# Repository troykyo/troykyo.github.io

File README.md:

This is a little site about Troy Nachtigall

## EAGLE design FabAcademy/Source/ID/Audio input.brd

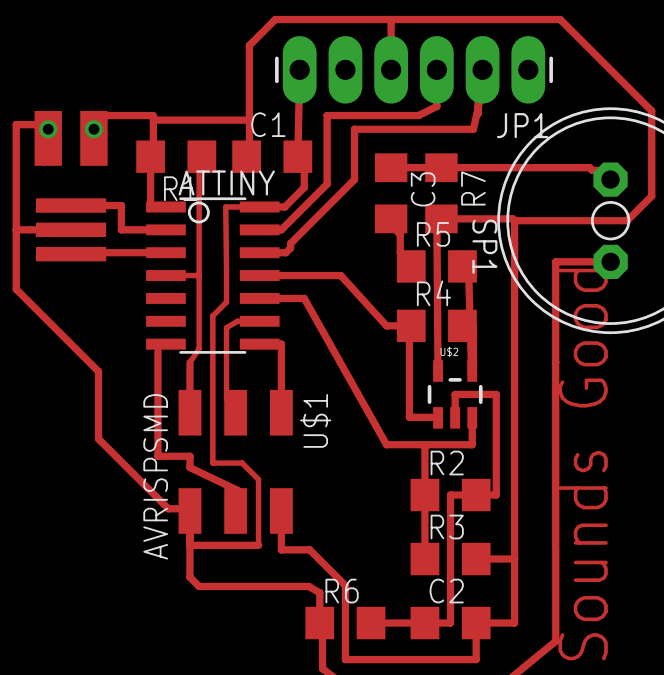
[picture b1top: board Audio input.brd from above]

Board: 2 copper layers, 16 parts (0 on the bottom side), 15 nets.

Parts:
ATTINY: ATTINY44-SSU; SOIC14
C1, C2, C3: 1206
JP1: 1X06_LONGPADS
QUARTZ: RESONATOR; EFOBM
R1, R2, R3, R4, R5, R6, R7: 1206
SP1: AL11P
U$1: AVRISPSMD; 2X03SMD
U$2: OPA344; SOT23-5

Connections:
GND: ATTINY.14, C1.2, C2.1, JP1.6, QUARTZ.2, R2.2, R6.1, R6.2, SP1.-, U$1.6, U$2.2
MIC+: C3.1, R7.1, SP1.+
MICCAP: C3.2, R5.1
MISO: ATTINY.8, U$1.1
MOSI: ATTINY.7, U$1.4
OPAI+: ATTINY.10, R2.1, R3.1, U$2.3
OPAI-: R4.2, R5.2, U$2.4
OPAOV: ATTINY.11, R4.1, U$2.1
RST: ATTINY.4, R1.1, U$1.5
RX: ATTINY.12, JP1.2
SCK: ATTINY.9, U$1.3
TX: ATTINY.13, JP1.3
VCC: ATTINY.1, C1.1, C2.2, JP1.4, R1.2, R3.2, R7.2, U$1.2, U$2.5
XTAL1: ATTINY.2, QUARTZ.3
XTAL2: ATTINY.3, QUARTZ.1

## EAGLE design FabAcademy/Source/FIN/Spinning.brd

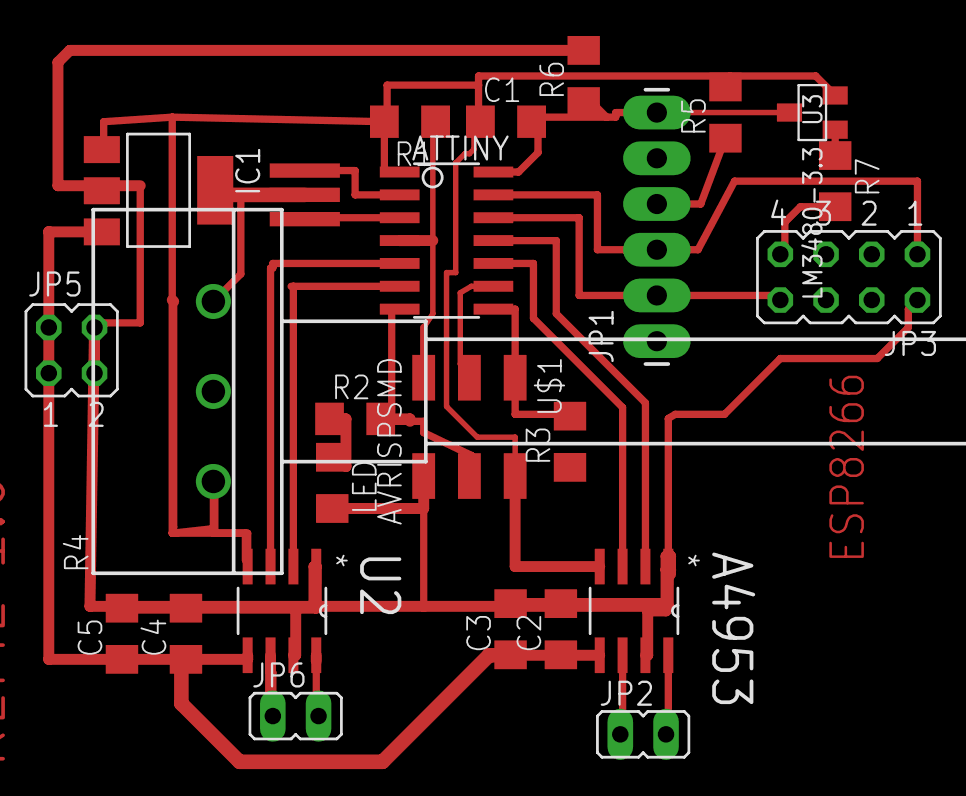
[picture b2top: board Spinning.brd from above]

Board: 2 copper layers, 25 parts (0 on the bottom side), 22 nets.

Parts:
A4953: ACS712ELCTR-05B-T; SOIC127P600X175-8N
ATTINY: ATTINY44-SSU; SOIC14
C1: 1uF; 1206
C2, C4: .1uF; 1206
C3, C5: 10uF; 1206
IC1: REG1118; SOT223
JP1: 1X06_LONGPADS
JP2, JP6: JP1
JP3: JP4Q
JP5: JP2Q
LED: 1206
QUARTZ: RESONATOR; EFOBM
R1: 10k; 1206
R2: 1K; 1206
R3: 1k; 1206
R4: CIP20C-6MM
R5, R6, R7: 0; 1206
U2: ACS712ELCTR-05B-T; SOIC127P600X175-8N
U3: LM3480-3.3; SOT-23-3
U$1: AVRISPSMD; 2X03SMD

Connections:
GND: A4953.1, A4953.7, ATTINY.14, C1.2, C2.2, C3.2, C4.2, C5.2, IC1.2, JP1.6, JP3.2, JP5.3, JP5.4, LED.2, QUARTZ.2, R4.E, R6.1, R6.2, U2.1, U2.7, U3.3, U$1.6
IN1A: A4953.3, ATTINY.10
IN1B: ATTINY.5, U2.3
IN2A: A4953.2, ATTINY.11
IN2B: ATTINY.6, U2.2
LEDRES: LED.1, R2.1
LEDRES1: R3.1, R4.S
MISO: ATTINY.8, R3.2, U$1.1
MOSI: ATTINY.7, R2.2, U$1.4
OUT1A: A4953.6, JP2.1
OUT1B: JP6.1, U2.6
OUT2A: A4953.8, JP2.2
OUT2B: JP6.2, U2.8
RST: ATTINY.4, R1.1, U$1.5
RX: ATTINY.12, JP1.2, JP3.8
SCK: ATTINY.9, U$1.3
TX: ATTINY.13, JP1.3, JP3.1
VBB: A4953.5, C2.1, C3.1, C4.1, C5.1, IC1.3, JP5.1, JP5.2, U2.5
VCC: A4953.4, ATTINY.1, C1.1, IC1.1, JP1.4, R1.2, R4.A, R5.1, R5.2, U2.4, U3.2, U$1.2
VCCESP: JP3.7, R7.1, R7.2, U3.1
XTAL1: ATTINY.2, QUARTZ.3
XTAL2: ATTINY.3, QUARTZ.1

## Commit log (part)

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2015-01-20 Initialization
2015-01-20 First Content
2015-01-20 First Post
2015-01-22 now with bootstrap
2015-01-22 Tom Theme Change
2015-01-22 Changed to Twitter theme.
2015-01-22 Name fix
2015-01-22 subheading fix
2015-01-22 Post fix
2015-01-24 restore
2015-01-24 Index Mod
2015-01-24 Index Mod2
2015-01-24 Index Mod3
2015-01-24 Index Mod 4
2015-01-24 Index Mod 5
2015-01-24 Index Mod 6
2015-01-24 Just a test
2015-01-24 Just a test 2
2015-01-24 Just a test 3
2015-01-24 Just a test 5
2015-01-24 Just a test 6
2015-01-24 Just a test 7
2015-01-24 Just a test 8
2015-01-25 Just a test 9
2015-01-25 New Site
2015-01-25 Images
2015-01-25 Images 2
2015-01-25 Images 3
2015-01-25 Images 4
2015-01-25 Images 6
2015-01-25 Pre Class update
2015-01-29 After the first lesson of Fab Academy
2015-01-31 Publishing
2015-02-01 refil inmage update
2015-02-02 changes to Final Project
2015-02-02 Final Project update
2015-02-03 documenting the error
2015-02-04 rebuilt the CSS with Sass
2015-02-06 Added Computer Aided Design
2015-02-07 Working on CAD
2015-02-08 Development Archive
2015-02-08 CAD changes
2015-02-09 css change
2015-02-09 at delcam crispin
2015-02-10 Now with CAD Source files
2015-02-14 optipng'd
2015-02-16 Cutting
2015-02-17 CUT update
2015-02-23 Electronics Production week 4
2015-02-24 Electronics Production Pics
2015-03-01 weekly update
2015-03-02 pics
2015-03-03 Picture weight reduction
2015-03-03 Image update
2015-03-09 Electronics Design
2015-03-17 Embedded Programming
2015-03-18 Restore of EP
2015-03-25 Milling
2015-04-14 input devices
2015-04-29 Composites
2015-04-30 Composite update
2015-05-15 Output
2015-05-20 3D switch
2015-05-20 Final
2015-05-23 index clean up
2015-06-02 presentation
2015-06-08 Final Project
2015-06-08 index update
2015-06-20 Composites compleation
2015-06-20 Composites Complete
2015-06-20 image compression
2015-06-20 FIN images
2015-06-21 Finally learned Mogrify
2015-06-21 Grooming the Documentation
2015-06-23 final updates
2015-06-23 Machine Building Add
2015-06-24 update final
2015-06-24 final update
2015-06-26 title update
2015-06-30 Interface m2m
2015-07-11 Minor changes for small things after local review.
2015-07-11 minor change Links.html
2015-08-11 Arturo Birth
2015-08-18 blah
2016-04-29 Create CNAME
    new domain
2016-04-29 troykyo.net master commmit
2016-04-29 troykyo.net update
2016-11-07 texbot test site
2016-11-07 cosmetic
2016-11-07 speed changes
2016-11-07 colors
2016-11-07 footer fix
2016-11-08 Editorial and Tracking
2016-11-08 smaller
2016-11-08 back to big
2016-11-08 Editorial
2016-11-08 image updates
2016-11-08 title change
2016-11-09 name
2016-11-09 fix pic
2016-11-09 Fix mess
2016-11-10 Marion
    I wrote my text. I will figure out how to put an image
2017-06-26 added Life
2019-08-11 Adding new dev site
    magenta is the new dev
2019-08-11 Forked the FabAcademy Site
2019-08-11 working footer links
2019-08-11 mogrified
2019-08-12 Sub Pages init
2019-08-12 small edits
2019-08-13 Launch main site, Fab Academy is the backup
2019-08-13 Create CNAME
2019-08-20 generic update
2019-08-20 page roll outs
2019-10-17 added circular
2019-10-21 added images
2019-10-21 challenges
2019-10-21 Finished Circular
2020-01-07 added portfolio
2020-01-07 added CV
2020-01-07 upate for sizing
2020-01-08 changed CV
    Index Menu Change
2020-01-08 cv updated
2020-03-03 content
2021-05-25 Create DataMaterialArduino.pdf
    Lesson 1
2021-05-26 Create DataasaMaterial-Tuning.pdf
    Todays lesson
2021-05-26 added slides
2021-05-26 changed slides
2021-05-27 NEw Slides
2021-05-27 sandwhich
2021-05-27 added breadboard
2021-05-27 added hook up of A0
2021-05-28 more slides
2023-08-30 added my .bib
2024-11-04 added new publications
2025-02-22 Adding portfloio update
2025-02-22 add project j
2025-02-22 fixed some spacing
2026-01-31 The BIG update from the Portflio
2026-01-31 new papers
2026-01-31 add pics
2026-02-02 Proofread a project check.
2026-02-09 Cookies?
2026-04-30 add slime mold
2026-06-03 removed Karlsruhl website
2026-06-05 udate
2026-06-09 pligramage 1st
2026-06-11 color an dmap
2026-06-13 logo change
2026-06-13 text
    i edited main body text
2026-06-13 map gange
2026-06-13 plan update
2026-06-15 Spelling Fuck up
2026-06-15 fonts
2026-06-16 Change of stay.
2026-06-16 Aurelio
2026-06-19 place
2026-06-22 color trail

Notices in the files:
parts and their libraries:
SparkFun-Connectors: Licensing: Creative Commons ShareAlike 4.0 International - https://creativecommons.org/licenses/by-sa/4.0
